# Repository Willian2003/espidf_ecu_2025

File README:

## Middle ECU

- micro-SD module storage
- CAN Logging 
- GPRS with MQTT comunication
- `Sends 20 packets to the server in 1 second`

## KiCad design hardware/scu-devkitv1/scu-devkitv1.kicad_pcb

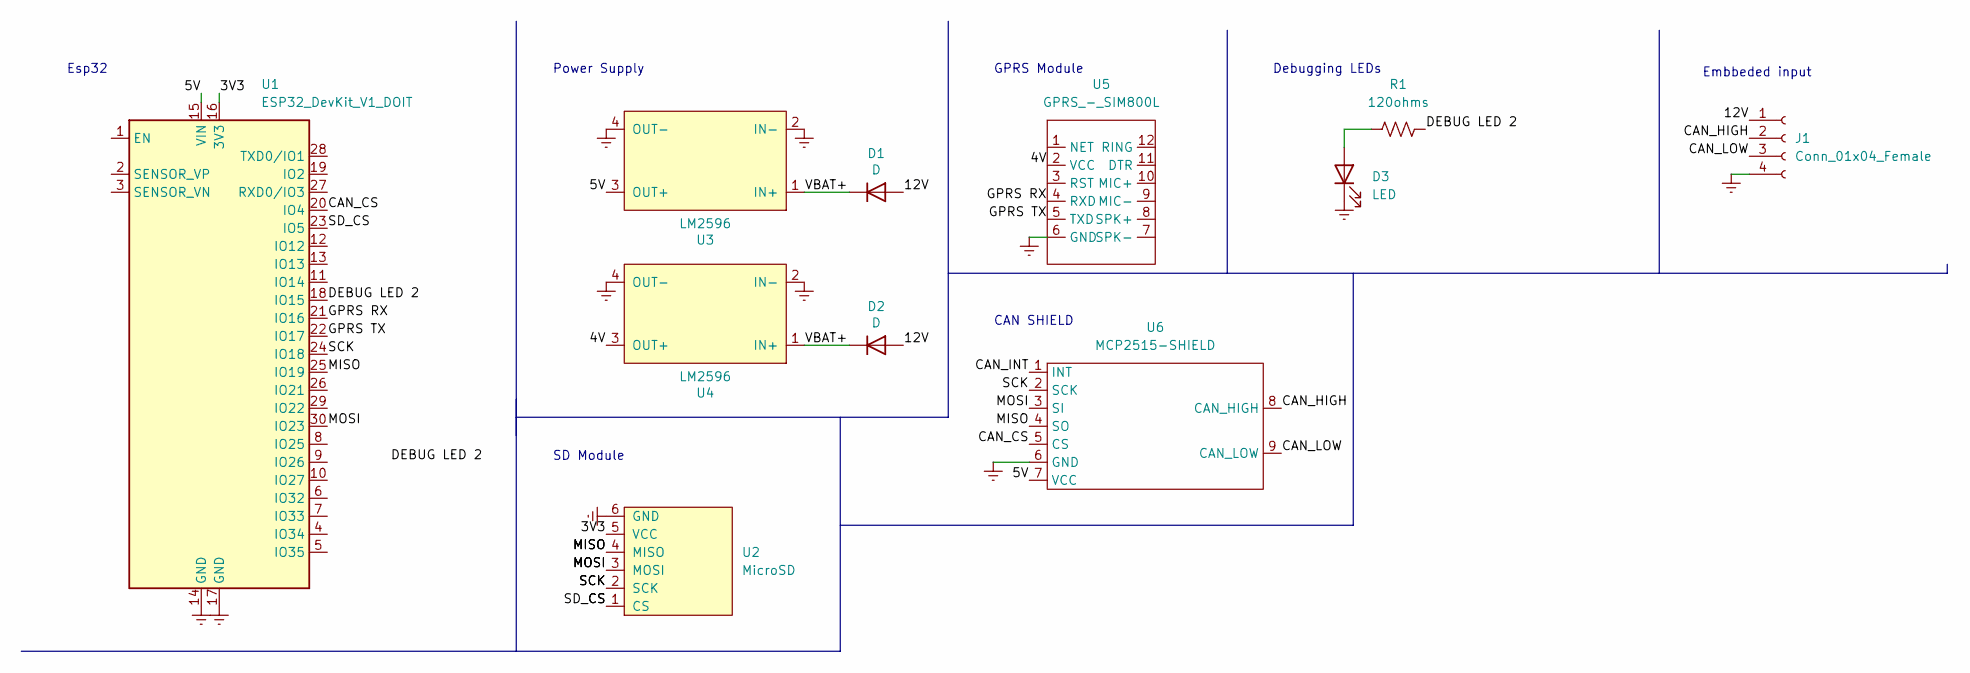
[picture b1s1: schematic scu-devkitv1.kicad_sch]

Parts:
D1, D2: D; schottky
D3: LED; LED_D3.0mm_Clear
J1: Conn_01x04_Female; Altech_AK300_1x04_P5.00mm_45-Degree
R1: 120ohms; R_Axial_DIN0207_L6.3mm_D2.5mm_P10.16mm_Horizontal
U1: ESP32_DevKit_V1_DOIT; esp32_devkit_v1_doit
U2: MicroSD; SCU_SD_mini
U3, U4: LM2596; LM2596 MINI 360
U5: GPRS_-_SIM800L; GPRS - SIM800L
U6: MCP2515-SHIELD

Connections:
/3V3: U1.16 (3V3), U2.5 (VCC)
/4V: U4.3 (OUT+), U5.2 (VCC)
/5V: U1.15 (VIN), U3.3 (OUT+), U6.7 (VCC)
/12V: D1.2 (A), D2.2 (A), J1.1
/CAN_CS: U1.20 (IO4), U6.5 (CS)
/CAN_HIGH: J1.2, U6.8 (CAN_HIGH)
/CAN_INT: U6.1 (INT)
/CAN_LOW: J1.3, U6.9 (CAN_LOW)
/CS: U1.23 (IO5), U2.1 (CS)
/DEBUG LED 2: R1.1, U1.18 (IO15)
/GPRS RX: U1.21 (IO16), U5.4 (RXD)
/GPRS TX: U1.22 (IO17), U5.5 (TXD)
/MISO: U1.25 (IO19), U2.4 (MISO), U6.4 (SO)
/MOSI: U1.30 (IO23), U2.3 (MOSI), U6.3 (SI)
/SCK: U1.24 (IO18), U2.2 (SCK), U6.2 (SCK)
/VBAT+: D1.1 (K), D2.1 (K), U3.1 (IN+), U4.1 (IN+)
Earth: D3.1 (K), J1.4, U1.14 (GND), U1.17 (GND), U2.6 (GND), U3.2 (IN-), U3.4 (OUT-), U4.2 (IN-), U4.4 (OUT-), U5.6 (GND), U6.6 (GND)
unnamed: D3.2 (A), R1.2

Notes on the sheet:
Debugging LEDs
Power Supply
CAN SHIELD
GPRS Module
SD Module
Esp32
Embbeded input

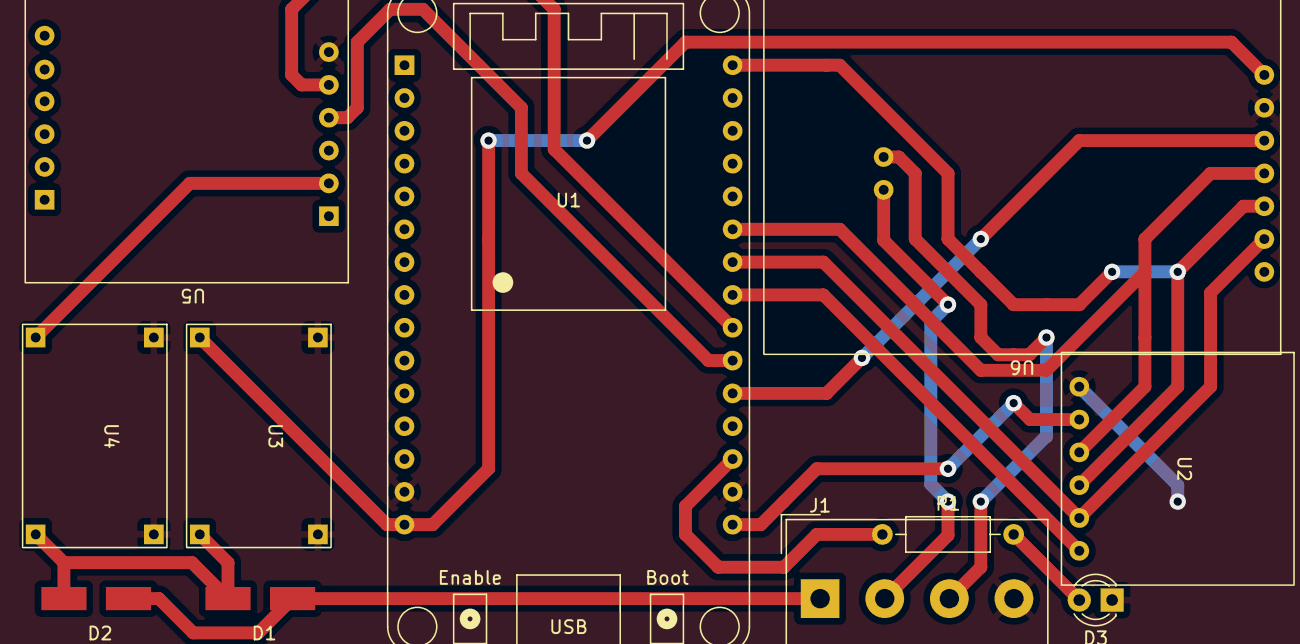
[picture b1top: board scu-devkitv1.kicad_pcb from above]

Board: 2 copper layers, 11 parts (0 on the bottom side), 17 nets.

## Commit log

2022-12-01 first commit, seeting up enviroment
2022-12-09 Framework change
2022-12-09 saving function created
2022-12-12 work on CAN communication
2022-12-14 Logic rework
2022-12-15 ready for logger testing
2022-12-15 sd bug solved
2023-01-02 Started working on hardware
2023-01-03 HARDWARE FINISHED
2023-01-05 Add GPRS functionality
2023-01-06 Add GPS functionality
2023-01-06 Comment out unnecessary "Serial.print"
2023-01-06 Complete the packet setup
2023-01-06 Complete packet in dataString
2023-01-11 Add Debug LED, fix CAN Interrupt
2023-01-11 Add CAN setup
2023-01-11 Fix CAN messages ID defs
2023-01-19 bug do sd corrigido
2023-01-20 Backup
2023-01-21 can teste
2023-01-25 logger working
2023-01-28 fix gprs pins
2023-01-28 switch gprs tx and rx
2023-02-07 GRPS working
2023-02-07 fix gprs pin
2023-02-07 GPRS Working
2023-02-09 fix mqtt conection
2023-02-10 Fix mqtt Reconecting
2023-02-10 Fix mqtt Reconecting bug
2023-02-12 Filter datas
2023-02-12 Filer datas
2023-02-12 fix volt data
2023-02-12 Change volt variable
2023-02-17 sending correctly datas for mqtt
2023-04-21 espidf 2023
2023-04-21 Nacional 2023 Version
2023-05-06 Remove mqttflag
2023-05-18 Change RPM json data
2023-05-26 Default config
2023-08-09 Add State of Telemetry
2023-08-11 Add SOT in publish packet
2023-08-12 Add fuel in can message
2023-08-13 Prototype to send the LAT and LNG for can
2023-08-21 Backup the main file for future actions
2023-08-21 Add CircularBuffer
2023-08-21 Organization of CAN ID's
2023-08-21 Spacing
2023-08-21 Organization of the structure for storage
2023-08-21 Added SCU state machines
2023-08-28 CAN and CircularBuffer working
2023-08-31 structure organization
2023-09-02 Change the buffer size
2023-09-02 functions declaration organized
2023-09-05 add chips definitions
2023-09-18 Change buffer size
2023-09-18 Comment GPS defines
2023-09-18 CHIP select and SOT flag
2023-09-20 Add reset flag of message function
2023-09-25 Add Debug for accx
2023-09-30 Add Titles in csv file
2023-09-30 Translate for english
2023-10-06 Camaçari coordinates
2023-10-06 Remove 2s ticker
2023-10-17 Change Volt and Current to float
2023-10-17 Change ID description
2023-10-18 Add ANGLE_ID
2023-10-18 Add angle struct
2023-10-18 Implement in CAN and packet the roll & picth angle
2023-10-22 Baja SAE Nordeste 2023
2023-10-25 Fix bug to Baja SAE Nordeste 2023
2023-11-25 Remove useless function
2023-11-29 Comment the GPS library
2023-11-29 Remove GPS pin
2023-11-29 Remove GPS State
2023-11-29 Change the sd ticker operation
2023-12-08 Change the pinout
2023-12-09 Comment old CAN lib
2023-12-09 Add CAN config
2023-12-09 Change the Pins to hardware_defs.h
2023-12-09 include gpio.h
2023-12-09 TJA1050/CAN-BUS Test receiver(OK!) and sender(testing)
2023-12-09 Remove MCP variables/declarations
2023-12-09 Include the Wifi communication
2023-12-09 Remove Datalogger ENUM
2023-12-09 Remove Saving Period
2023-12-09 Add CLEAR define
2023-12-09 CAN-BUS communication OK!
2023-12-26 Update the CAN variables
2023-12-30 Add default struct
2023-12-30 Add all includes
2023-12-30 Change the name of struct
2023-12-30 Change to the main the SD variables
2024-01-03 Add ID identifier for Baja prototypes
2024-01-05 Change Queue size
2024-01-05 Change the doc(Json packet) size
2024-01-11 Change the queue receive time
2024-01-15 Nacional 2024v
2024-01-23 Add CAN status enum
2024-01-30 Add timeout for mqtt conectivity
2024-02-15 Commit CAN libs
2024-02-15 Add CAN lib
2024-02-15 CAN working with SD and GPRS
2024-02-20 Test send bytes to node-red
2024-02-22 send bytes ok
2024-02-23 Set max message buffer
2024-02-23 Sending 20 packets in bytes
2024-03-08 Change the GPRS pin
2024-03-09 Nacional 2024v | CAN update
2024-04-07 New functions in CANmsg.h
2024-05-03 Resume the ECU code
2024-05-03 Update README file
2024-05-03 Fix submodule error
2024-05-03 Add gitmodules file
2024-05-03 Fix the sequencial logic of firmware
2024-05-03 Fix function declaration
2024-05-03 Fix msg packet update
2024-05-03 Add OTA functions librarie
2024-05-03 remove submodule
2024-05-03 Add submodule
2024-05-04 Test v2
2024-05-04 remove struct pointer
2024-05-04 Test 3
2024-05-04 Test 4
2024-05-04 Add a flag when the CAN is started!
2024-05-05 Fix SD storage data
2024-05-06 Add the Wifi Manager lib
2024-05-06 FEAT: OTA, add callback when is conected in Wifi
2024-05-10 Add ota config
2024-05-10 Updata wifi connection
2024-05-10 Add serial print when start the OTA server
2024-06-06 Remove OTA librarie
2024-07-11 update git ignore
2024-07-11 Update firmware
2024-12-18 Implement the BLE debug
2024-12-18 Decrease BLE_REQUEST delay & remove useless bitwise
2024-12-18 Fix variable value
2024-12-18 Move the defines to the include folder
2024-12-20 Change the SCU_ID bits message
2024-12-27 Remove useless lib
2025-02-24 plotando variaveis pra ver bits
2025-03-07 Atualizando para o servidor atual
    Finalizado os teste, agora o codigo foi atualizado para direcionar os dados para o novo servidor
2025-03-10 Colando o Serial.Begin
    Tava sem o Serial.Begin, um dos provaveis motivos do pq estava falando o código
2025-03-10 Teste 1
2025-06-19 Implement web-based OTA updater
2025-06-20 Uncommented ConnStateMachine
